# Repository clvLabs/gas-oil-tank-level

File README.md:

# gas-oil-tank-level

Easy gas oil tank level meter using an Arduino and a *ping* sensor

## Hardware

* Arduino Nano
* Ping sensor
* OLED screen
  * 2 3K3 resistors (I2C pullups)
* 2 buttons
  * 2 10K resistors (pullups)

## Software

### Requirements

This project has been developed with PlatformIO, you can compile it with the stock Arduino IDE, but you'll have a nicer time with PlatformIO...

### Configuration

Keeping both buttons pressed for `BUTTON_HOLD_TIME` will enter configuration mode, in which you can set `MIN_LEVEL_CM` and `MAX_LEVEL_CM`. These settings will be stored on EEPROM.

To change other settings you have to edit `src/config.h`.

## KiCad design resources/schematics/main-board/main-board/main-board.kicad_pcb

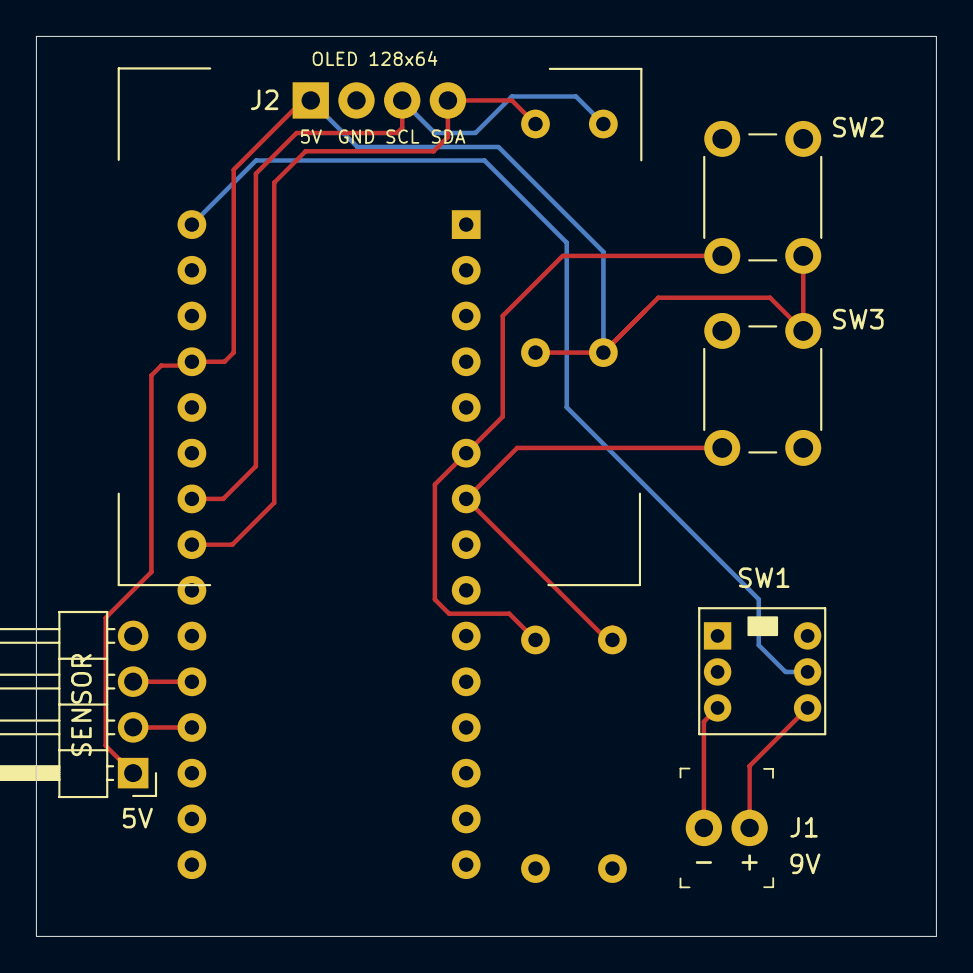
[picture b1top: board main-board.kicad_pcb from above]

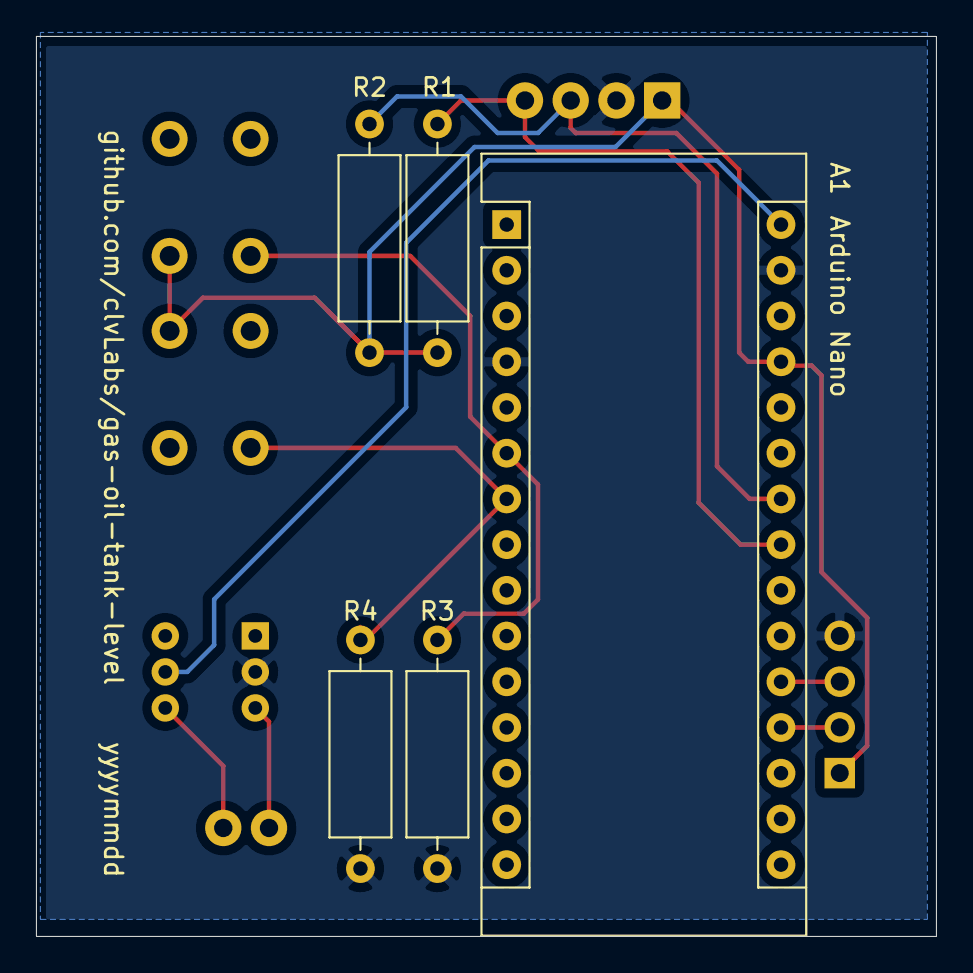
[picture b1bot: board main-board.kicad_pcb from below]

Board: 2 copper layers, 50.0 x 50.0 mm, 11 parts (5 on the bottom side), 11 nets.

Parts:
A1: Arduino_Nano_v3.x; Arduino_Nano
J1: Conn_01x02_Female; PinHeader_1x2_P2.54mm_Drill1.02mm
J2: Conn_01x04_Female; OLED_128X64
J3: Conn_01x04_Female; PinHeader_1x04_P2.54mm_Horizontal
R1, R2: 3.3K; R_Axial_DIN0309_L9.0mm_D3.2mm_P12.70mm_Horizontal
R3, R4: 10K; R_Axial_DIN0309_L9.0mm_D3.2mm_P12.70mm_Horizontal
SW1: SW_Push_DPDT; Switch_DPDT_7x7mm
SW2, SW3: SW_Push_45deg; SW_PUSH_6mm_H7.3mm

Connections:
+5V: A1.27, J2.1, J3.1, R1.1, R2.1, SW2.2, SW3.2
BATT_GND: J1.1, SW1.3
BATT_VIN: J1.2, SW1.6
BUTTON_DOWN_PIN: A1.7, R4.2, SW3.1
BUTTON_UP_PIN: A1.6, R3.2, SW2.1
GND: A1.4, A1.29, J2.2, J3.4, R3.1, R4.1, SW1.2
I2C_SCL: A1.24, J2.3, R2.2
I2C_SDA: A1.23, J2.4, R1.2
PING_ECHO_PIN: A1.20, J3.3
PING_TRIGGER_PIN: A1.19, J3.2
VIN: A1.30, SW1.5

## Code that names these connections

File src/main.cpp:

#include "Arduino.h"
#include "3rdParty/JC_Button/JC_Button.h"
#include "config.h"
#include "utils/eepromcfg.h"
#include "ui/uimgr.h"

// Globals
DISPLAY_CLASS u8g(U8G_I2C_OPT_NONE | U8G_I2C_OPT_DEV_0); // I2C / TWI
Button btnUp(BUTTON_UP_PIN, BUTTON_DEBOUNCE_MS, BUTTON_INTERNAL_PULLUP, BUTTON_INVERT);
Button btnDown(BUTTON_DOWN_PIN, BUTTON_DEBOUNCE_MS, BUTTON_INTERNAL_PULLUP, BUTTON_INVERT);
ui::UIMgr uiMgr;
EEPROMCfg cfg;

void setup()
{
#ifdef SERIAL_OUTPUT_ENABLED
    Serial.begin(9600);
    Serial.println("Jelou!");
#endif

    pinMode(PING_TRIGGER_PIN, OUTPUT);
    pinMode(PING_ECHO_PIN, INPUT);

    pinMode(BUTTON_UP_PIN, INPUT);
    pinMode(BUTTON_DOWN_PIN, INPUT);

    u8g.setColorIndex(1);
    btnUp.begin();
    btnDown.begin();

    uiMgr.setup(&cfg, &u8g, &btnUp, &btnDown);
}

void loop()
{
    uiMgr.loop();
    delay(LOOP_SLEEP_MS);
}

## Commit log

2019-12-21 Initial (empty) commit
2019-12-21 Initial prototype
2019-12-28 Switch to Arduino Nano
2019-12-28 Calculate tank%
2019-12-28 Center texts / use different fonts
2019-12-28 Show bar / voltage
2019-12-28 Make serial output optional
2019-12-28 Add 100% marker
2019-12-28 Add "alive" blink indicator
2019-12-28 Blink battery voltage as alarm
2019-12-28 Reorganize code
2020-01-30 Allow 0 distance
2020-01-31 Add schematic/pcb
2020-01-31 Ignore local user files
2020-02-12 Calibrate BOTTOM_CM for my tank
2020-02-12 Add README
2020-02-13 Calibrate TOP_CM for my tank
2020-10-15 Add config / refactor
2020-10-15 Rename ui/states/config as settings
2020-10-15 Add ramp mode for buttons
2020-10-15 Add MEASURECM state
2020-10-16 Read distances with ping_median()
2020-10-16 Add board 3D model
2020-10-16 #include cleanup
2020-10-16 Add pct bar center line
2020-10-17 Rename project
2020-12-31 Refactor PCB - batch-20201231
2020-12-31 Update calibration for my tank
2021-01-10 Add horizontal pin header for connector
2021-01-17 Update footprints
2021-11-14 Add 3D files
